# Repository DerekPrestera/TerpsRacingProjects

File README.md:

# TerpsRacingProjects

Hello! This is where I host the projects I'm working on (or have worked on) for the University of Maryland, College Park's engineering competition team for the Society of Automotive Engineering Formula student competition (FSAE). I create work for both the Electric vehicle (EV) and Internal Combustion Engine (ICE) teams.

# Brief Overview
I am currently working on the following projects:
- CANbus Module Shield
- Telemetry Viewer

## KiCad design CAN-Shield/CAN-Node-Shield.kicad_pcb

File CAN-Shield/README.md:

# Terps Racing CAN Module Shield for Arduino Uno

This board is the basis for a CAN network based sensor system for Terps Racing vehicles. It is a shield for Arduino uno that allows the Arduino to communicated on a CAN netowrk with the MCP2515 CAN to SPI chip and read analog sensor data with 12-bit resolution with the MCP3208 ADC chip. This turns the Arduino into a data collection CAN Node that can be placed right next to the location of a sensor and transmit its reading to the vehicle's CAN bus for logging, telemetry, or possibly use by data-driven active components elsewhere on the vehicle.

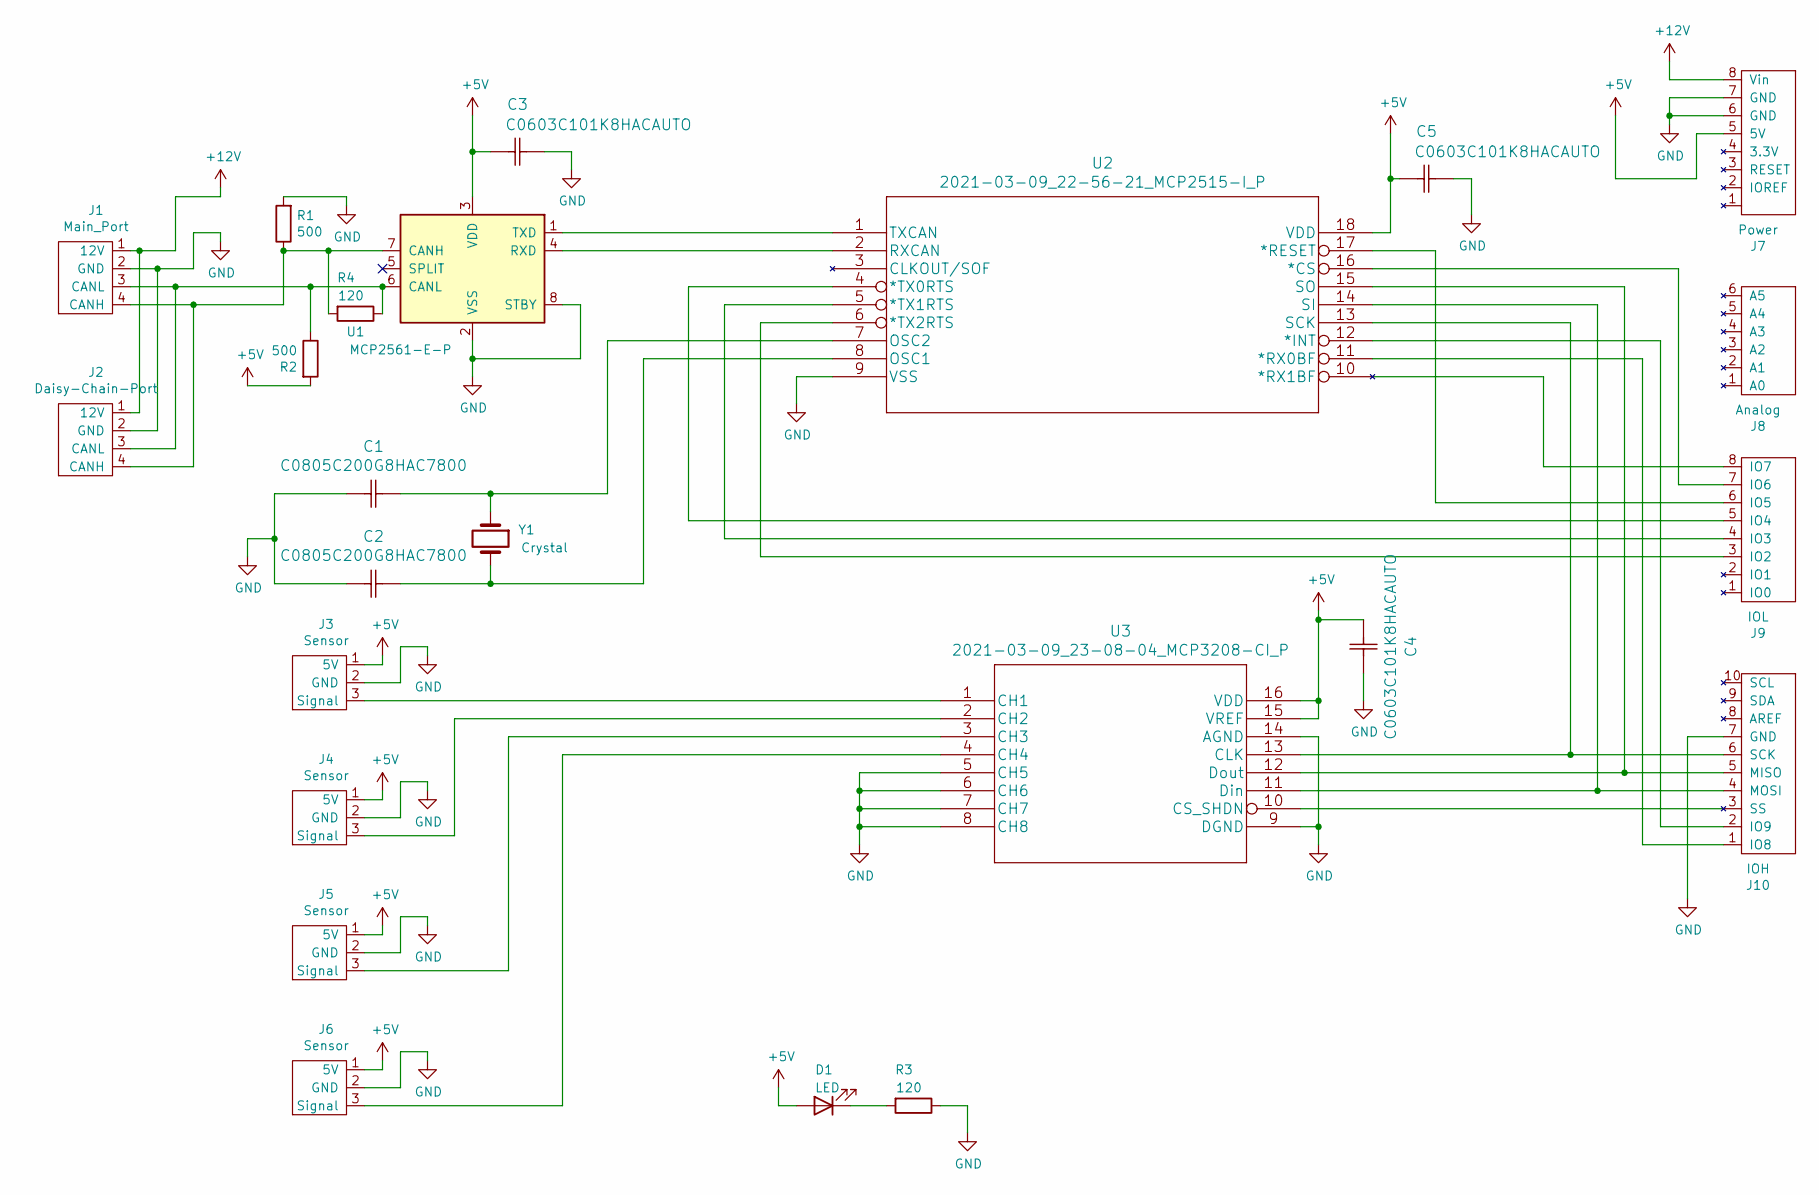
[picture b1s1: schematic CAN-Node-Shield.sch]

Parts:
C1, C2: C0805C200G8HAC7800; C_Rect_L7.0mm_W2.5mm_P5.00mm
C3, C4, C5: C0603C101K8HACAUTO; C_Rect_L4.0mm_W2.5mm_P2.50mm
D1: LED; LED_D5.0mm_FlatTop
J1: Main_Port; PinHeader_1x04_P2.54mm_Vertical
J2: Daisy-Chain-Port; PinHeader_1x04_P2.54mm_Vertical
J3, J4, J5, J6: Sensor; PinHeader_1x03_P2.54mm_Vertical
J7: Power; PinSocket_1x08_P2.54mm_Vertical
J8: Analog; PinSocket_1x06_P2.54mm_Vertical
J9: IOL; PinSocket_1x08_P2.54mm_Vertical
J10: IOH; PinSocket_1x10_P2.54mm_Vertical
R1, R2: 500; R_Axial_DIN0207_L6.3mm_D2.5mm_P10.16mm_Horizontal
R3, R4: 120; R_Axial_DIN0207_L6.3mm_D2.5mm_P10.16mm_Horizontal
U1: MCP2561-E-P; DIP-8_W7.62mm
U2: 2021-03-09_22-56-21_MCP2515-I_P; DIP-18_W7.62mm
U3: 2021-03-09_23-08-04_MCP3208-CI_P; DIP-16_W7.62mm
Y1: Crystal; Crystal_HC49-U_Vertical

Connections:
+5V: C3.1, C4.1, C5.1, D1.2 (A), J3.1 (5V), J4.1 (5V), J5.1 (5V), J6.1 (5V), J7.5 (5V), R2.2, U1.3 (VDD), U2.18 (VDD), U3.15 (VREF), U3.16 (VDD)
+12V: J1.1 (12V), J2.1 (12V), J7.8 (Vin)
GND: C1.1, C2.1, C3.2, C4.2, C5.2, J1.2 (GND), J2.2 (GND), J3.2 (GND), J4.2 (GND), J5.2 (GND), J6.2 (GND), J7.6 (GND), J7.7 (GND), J10.7 (GND), R1.2, R3.1, U1.2 (VSS), U1.8 (STBY), U2.9 (VSS), U3.5 (CH5), U3.6 (CH6), U3.7 (CH7), U3.8 (CH8), U3.9 (DGND), U3.14 (AGND)
unnamed: C1.2, U2.7 (OSC2), Y1.1
unnamed: C2.2, U2.8 (OSC1), Y1.2
unnamed: D1.1 (K), R3.2
unnamed: J1.3 (CANL), J2.3 (CANL), R2.1, R4.1, U1.6 (CANL)
unnamed: J1.4 (CANH), J2.4 (CANH), R1.1, R4.2, U1.7 (CANH)
unnamed: J3.3 (Signal), U3.1 (CH1)
unnamed: J4.3 (Signal), U3.2 (CH2)
unnamed: J5.3 (Signal), U3.3 (CH3)
unnamed: J6.3 (Signal), U3.4 (CH4)
unnamed: J9.3 (IO2), U2.6 (*TX2RTS)
unnamed: J9.4 (IO3), U2.5 (*TX1RTS)
unnamed: J9.5 (IO4), U2.4 (*TX0RTS)
unnamed: J9.6 (IO5), U2.17 (*RESET)
unnamed: J9.7 (IO6), U2.16 (*CS)
unnamed: J9.8 (IO7), U2.10 (*RX1BF)
unnamed: J10.1 (IO8), U2.11 (*RX0BF)
unnamed: J10.2 (IO9), U2.12 (*INT)
unnamed: J10.3 (SS), U3.10 (CS_SHDN)
unnamed: J10.4 (MOSI), U2.14 (SI), U3.11 (Din)
unnamed: J10.5 (MISO), U2.15 (SO), U3.12 (Dout)
unnamed: J10.6 (SCK), U2.13 (SCK), U3.13 (CLK)
unnamed: U1.1 (TXD), U2.1 (TXCAN)
unnamed: U1.4 (RXD), U2.2 (RXCAN)

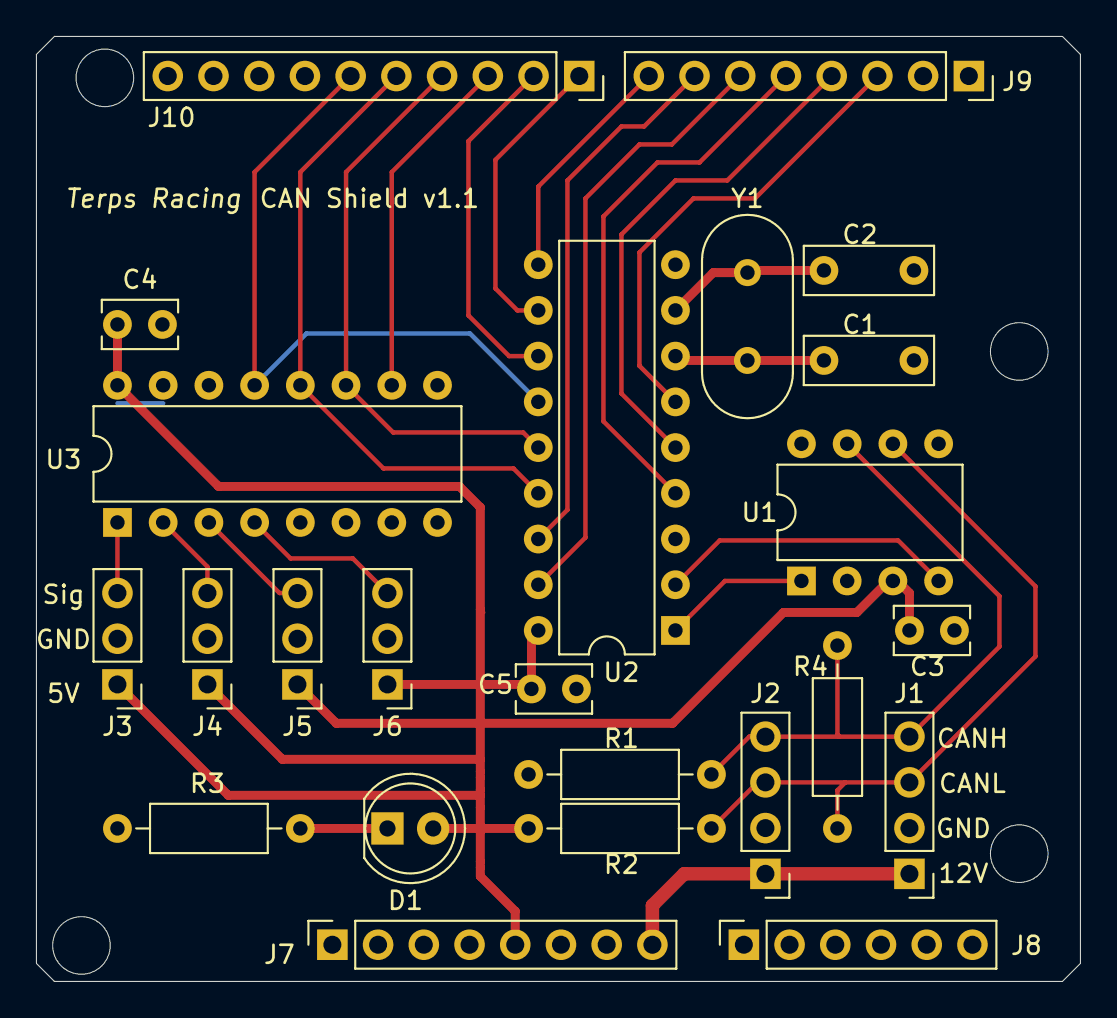
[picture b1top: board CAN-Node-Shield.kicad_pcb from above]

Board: 2 copper layers, 58.0 x 52.5 mm, 24 parts (0 on the bottom side), 26 nets.

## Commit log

2021-04-21 Initial readme creation
2021-04-21 Created a readme for a slight introduction
2021-04-21 This is the first version of the program uploaded
    At the moment the program is designed to just read data from the serial port and plot it. The data coming in is formatted specially for this program. Since the transmitting MCU is also programmed by 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
2021-04-21 Corrected overview list with "shield"
2021-04-22 Initial readme file with brief description
2021-04-22 pic of the pcb
2021-04-22 include a picture
2021-04-25 Program used to simulate transmitted data
    This is the Arduino program that was used to generate a triangle wave that simulated data that was sent over serial from the Arduino to the computer. It formats the data the way the program expects t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
2021-04-26 CAN terminating resistor change
    I updated the layout to include options for both High-speed CAN and Low-speed CAN terminating resistor configurations. There are positions for either type of termination so the board can be used for 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
2021-06-11 Updated the picture of the PCB layout
2021-06-11 Uploading CAN shield Arduino Sketch
    This is the template for the Arduino sketch that includes all of the definitions and functions that are used to operate the CAN shield. Currently only the function to receive CAN messages is implemen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
2021-08-20 Simplified buffer address arrays; renamed funcs
2021-09-10 Informational silkscreen and new board footprint
    Changes made:
    - Adjusted bottom two Arduino headers; they were too far to the left by 2mm
    - Added silkscreen labels to header pins for easy identification of pin function
    - Reduced board footprint to allow for smaller enclosures
    - Chamfered corners to prevent them from being too pointy
    - Added my name :)
2021-09-10 Updated description; changed pic to updated board
2021-09-10 Removed CAN shield sketch to replace with library
2021-09-10 Arduino library for use with the CAN shield
2021-09-20 Added CAN ID parameter to constructor
2021-09-21 Fixed: tx rx reg addr arrays, class definition
2021-10-12 Added ability to toggle debug messages
    Added a define to toggle debug messages during the initialization of the CAN shield object. This is also an upload of the uncompressed library so it is easier to view here.
2021-10-12 Define to toggle debug messages - compressed lib
    Added a define to toggle debug messages. This is the compressed library for download and use.
2021-10-26 Alternated ADC inputs
    Changes:
    - Changed the ADC input ports to be connected to alternating ADC chip inputs to separate the traces to help reduce potential for cross-talk.
    - Increased the width of the trace between the 12V power ports to allow for increased current capacity since this trace will carry power for all downstream devices.
2021-10-26 Uploaded Gerber Files
    Uploaded the Gerber files generated from the most recent PCB updates so the team can order some boards.
2022-02-16 Added examples for CAN send and CAN receive
2022-05-08 Implemented Analog Channel Selection
    Implemented channel selection for the analogRead() method. The previous implementation was quickly written for board testing but did not utilize the channel selection parameter and only read from cha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
